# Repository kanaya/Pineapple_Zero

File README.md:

# Pineapple Zero

Pineapple Zero is a MIDI extender. It can receive MIDI signal from normal MIDI-IN connector and repeat that signal by using RS-422 driver. It also can receive extended MIDI signal and repeat that signal to normal MIDI-OUT connector.

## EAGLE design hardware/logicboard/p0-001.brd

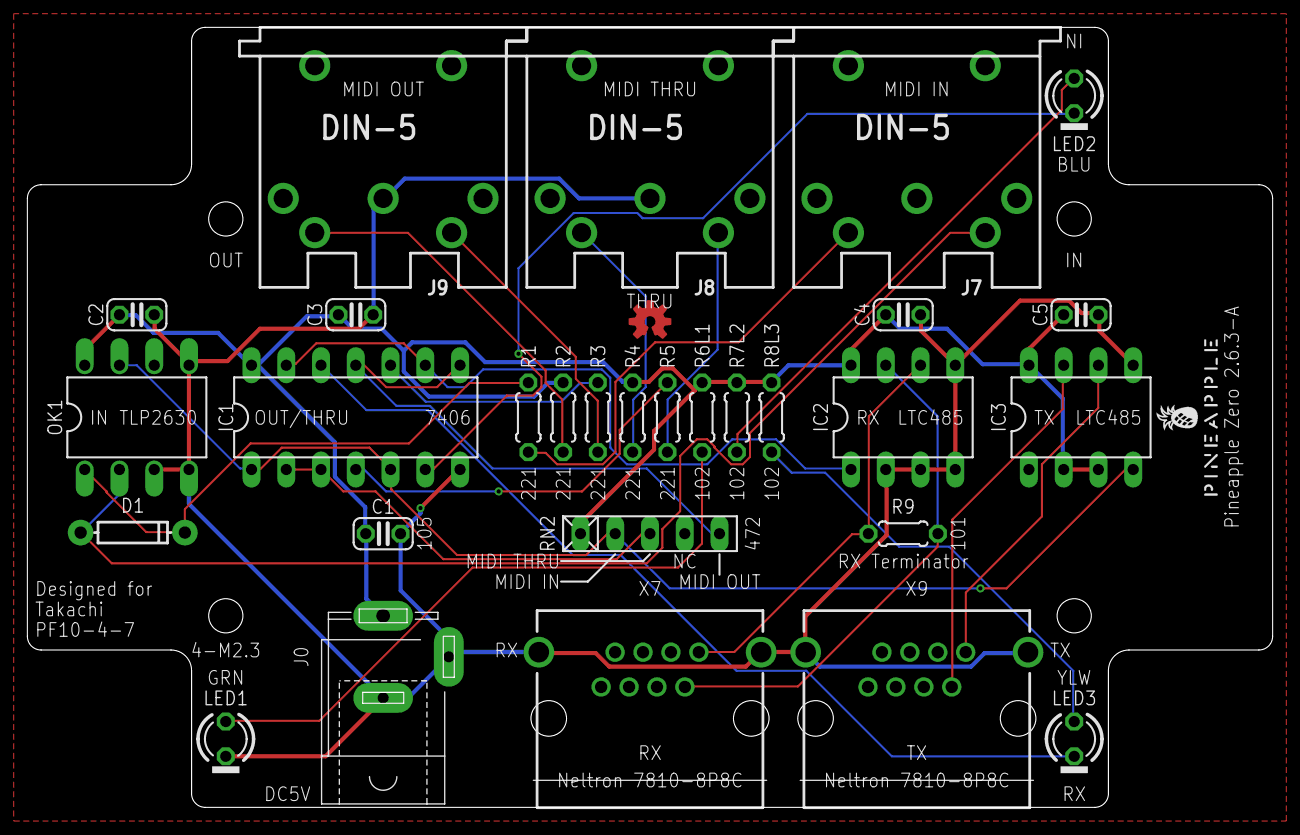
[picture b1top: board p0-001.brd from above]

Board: 2 copper layers, 91.0 x 57.0 mm, 31 parts (0 on the bottom side), 24 nets.

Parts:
C1: 100n; C025-024X044
C2, C3, C4, C5: 10n; C025-024X044
D1: DIODE-1N4148
IC1: 74ALS05N; DIL14
IC2, IC3: LTC485N; DIL08
J0: DC5V; SPC4077
J7, J8, J9: DIN5; DIN5-RA-PTH
LED1: BLUE; LED3MM
LED2, LED3: YELLOW; LED3MM
LOGO1: OSHW-LOGOS-COPPER; OSHW-LOGO-S_COPPER
OK1: HCPL2630; DIL08
R1, R2, R3, R4, R5: 220; 0204/5
R6L1, R7L2, R8L3: 1k; 0204/5
R9: 100; 0204/5
RN2: 4.7k; RN-5
U$1: PINEAPPLE450
X7, X9: NELTRON-7810-XPXC; NELTRON-7810-XPXC-FOOTPRINT

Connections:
GND: C1.2, C2.2, C3.2, C4.2, C5.2, IC1.7, IC2.2, IC2.3, IC2.4, IC2.5, IC3.5, J0.1, J0.2, J8.2, J9.2, LED1.K, OK1.3, OK1.4, OK1.5, X7.S1, X7.S2, X9.S1, X9.S2
MIDIIN: D1.C, OK1.1, R1.2
MIDIOUT: IC1.10, R3.2
MIDITHRU: IC1.4, R5.2
MIRTN: D1.A, J7.5, OK1.2
MISND: J7.4, R1.1
MORTN: J9.5, R3.1
MOSND: J9.4, R2.1
MTRTN: J8.5, R5.1
MTSND: J8.4, R4.1
unnamed: IC1.6, LED2.K
unnamed: LED3.A, R8L3.1
unnamed: IC1.12, LED3.K
unnamed: LED1.A, R6L1.1
unnamed: LED2.A, R7L2.1
NMIDIOUT: IC1.8, IC1.11, RN2.5
NMIDITHRU: IC1.2, IC1.3, RN2.3
RX: IC1.9, IC1.13, IC2.1
RX+: IC2.6, R9.1, X7.1
RX-: IC2.7, R9.2, X7.2
TX: IC1.1, IC1.5, IC3.4, OK1.7, RN2.2
TX+: IC3.6, X9.1
TX-: IC3.7, X9.2
VCC: C1.1, C2.1, C3.1, C4.1, C5.1, IC1.14, IC2.8, IC3.2, IC3.3, IC3.8, J0.3, OK1.8, R2.2, R4.2, R6L1.2, R7L2.2, R8L3.2, RN2.1

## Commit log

2018-07-19 Initial commit.
2018-07-19 Silk.
2018-07-19 New layout.
2018-07-19 Fixed silk of the panel.
2018-07-26 Component list.
2018-07-26 Fixed component list.
2018-07-26 Document update.
2018-08-03 Clean up.
2018-08-04 1mm exterior.
2018-08-09 1mm-exterior.
2018-08-09 Changed signal names.
2018-08-10 Doc.
2018-08-11 OSHW logo.
2018-08-13 Pineapple logo v2.
2018-08-13 New pineapple logo.
2018-08-14 Updated silk pattern.
2018-08-14 Replaced D1.
2018-08-14 Added clean target to Makefile.
2018-08-15 Version 1.0.1 -> 1.1.0.
2018-08-21 Pineapple Logo (vector->bitmap), OSHW logo (silk -> copper).
2018-08-22 Changed font size of the silk pattern.
2018-09-05 Unified MIDI connector.
2018-09-16 Route change.
2018-09-16 Silk update.
2018-09-16 Clean up of the schematic.
2018-09-16 Clean up of panel design.
2018-09-16 Added screenshot of the schematic (release/1.2.0).
2018-09-16 Added partlist.
2022-01-26 First try.
2022-01-26 Rounded corners.
2022-01-26 Rounded corners (again).
2022-01-27 Now use Neltron's RJ-45 Jack.
2022-01-28 Routed.
2022-01-28 Swapped IC2 and IC3.
2022-01-28 Rearranged connectors.
2022-01-28 Added values of components.
2022-01-28 Now MIDI IN-OUT-THRU line up.
2022-01-29 Silk, layout, etc.
2022-01-29 Layout of LED.
2022-02-09 Version number to 2.0.1.
2022-02-15 Removed Makefile, files.txt, and panel layout.
2022-03-30 Updated RJ45 connectors.
2022-04-04 Fixed pull-up.
2022-04-04 Swapped MIDI IN and THRU, TX and RX.
2022-04-05 Changed wiring of MIDI IN LED.
2022-04-05 Changed Rs for LEDs.
2022-04-06 Added MIDI signal checker.
2022-08-03 Changed led connection.
2022-08-03 Silk. 2.0.1-B.
2022-08-17 Connector name.
2022-08-18 Swapped MIDI THRU and OUT.

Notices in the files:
parts and their libraries:
SparkFun-Aesthetics: Licensing: Creative Commons ShareAlike 4.0 International - https://creativecommons.org/licenses/by-sa/4.0
